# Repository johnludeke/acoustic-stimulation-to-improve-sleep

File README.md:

# Acoustic Stimulation to Improve Sleep

This repo will contain all code and notebooks related to our senior design project.

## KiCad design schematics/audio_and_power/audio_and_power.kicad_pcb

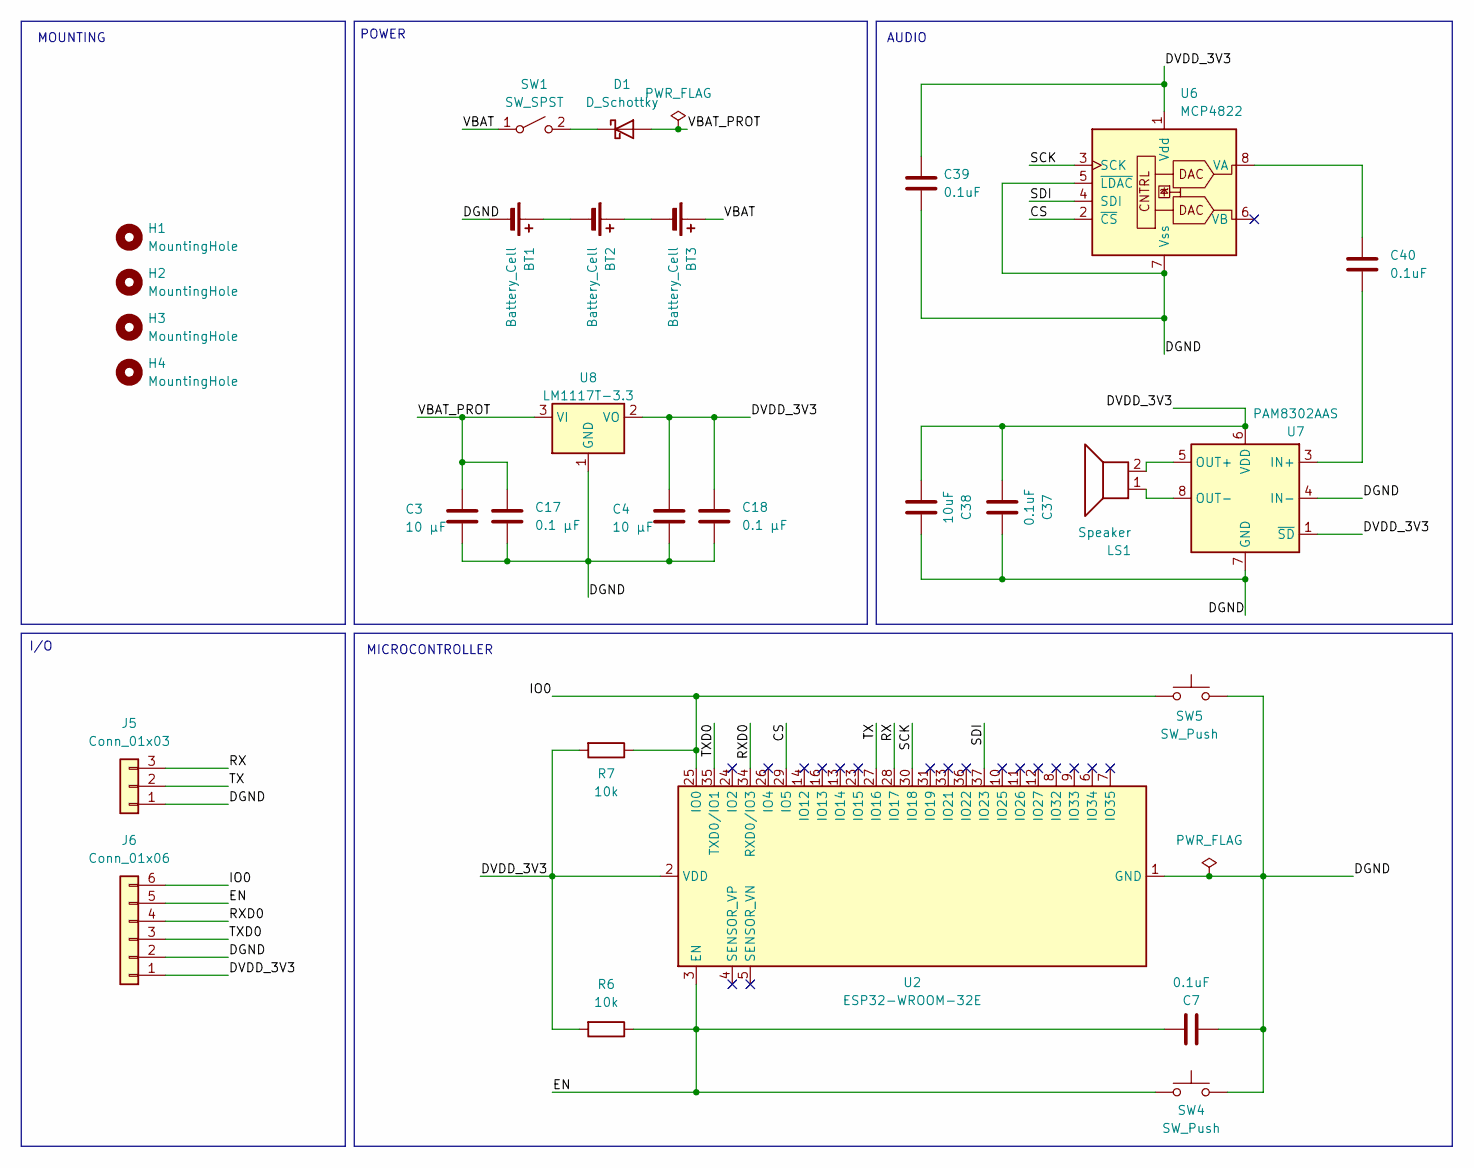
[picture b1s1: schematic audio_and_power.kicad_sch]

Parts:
BT1, BT2, BT3: Battery_Cell; PinHeader_1x02_P2.54mm_Vertical
C3, C4: 10 µF; C_0603_1608Metric
C7, C37, C39, C40: 0.1uF; C_0603_1608Metric
C17, C18: 0.1 µF; C_0603_1608Metric
C38: 10uF; C_0805_2012Metric
D1: D_Schottky; D_SOD-123
H1, H2, H3, H4: MountingHole; MountingHole_3.2mm_M3
J5: Conn_01x03; PinHeader_1x03_P2.54mm_Vertical
J6: Conn_01x06; PinHeader_1x06_P2.54mm_Vertical
LS1: Speaker; PinHeader_1x02_P2.54mm_Vertical
R6, R7: 10k; R_0603_1608Metric
SW1: SW_SPST; SW_DIP_SPSTx01_Slide_6.7x4.1mm_W8.61mm_P2.54mm_LowProfile
SW4, SW5: SW_Push; SW_SPST_TL3342
U2: ESP32-WROOM-32E; ESP32-WROOM-32D
U6: MCP4822; MSOP-8_3x3mm_P0.65mm
U7: PAM8302AAS; MSOP-8_3x3mm_P0.65mm
U8: LM1117T-3.3; TO-220-3_Horizontal_TabDown

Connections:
/CS: U2.29 (IO5), U6.2 (~CS)
/DGND: BT1.2 (-), C3.2, C4.2, C7.1, C17.2, C18.2, C37.2, C38.2, C39.2, J5.1, J6.2, SW4.2, SW5.2, U2.1 (GND), U2.15 (GND), U2.38 (GND), U2.39 (GND), U6.5 (~LDAC), U6.7 (Vss), U7.4 (IN-), U7.7 (GND), U8.1 (GND)
/DVDD_3V3: C4.1, C18.1, C37.1, C38.1, C39.1, J6.1, R6.2, R7.2, U2.2 (VDD), U6.1 (Vdd), U7.1 (~SD), U7.6 (VDD), U8.2 (VO)
/EN: C7.2, J6.5, R6.1, SW4.1, U2.3 (EN)
/IO0: J6.6, R7.1, SW5.1, U2.25 (IO0)
/RX: J5.3, U2.28 (IO17)
/RXD0: J6.4, U2.34 (RXD0/IO3)
/SCK: U2.30 (IO18), U6.3 (SCK)
/SDI: U2.37 (IO23), U6.4 (SDI)
/TX: J5.2, U2.27 (IO16)
/TXD0: J6.3, U2.35 (TXD0/IO1)
/VBAT: BT3.1 (+), SW1.1 (A)
/VBAT_PROT: C3.1, C17.1, D1.2 (A), U8.3 (VI)
unnamed: BT1.1 (+), BT2.2 (-)
unnamed: BT2.1 (+), BT3.2 (-)
unnamed: D1.1 (K), SW1.2 (B)
unnamed: C40.1, U6.8 (VA)
unnamed: C40.2, U7.3 (IN+)
unnamed: LS1.2, U7.5 (OUT+)
unnamed: LS1.1, U7.8 (OUT-)

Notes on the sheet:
I/O
MOUNTING
AUDIO
MICROCONTROLLER
POWER

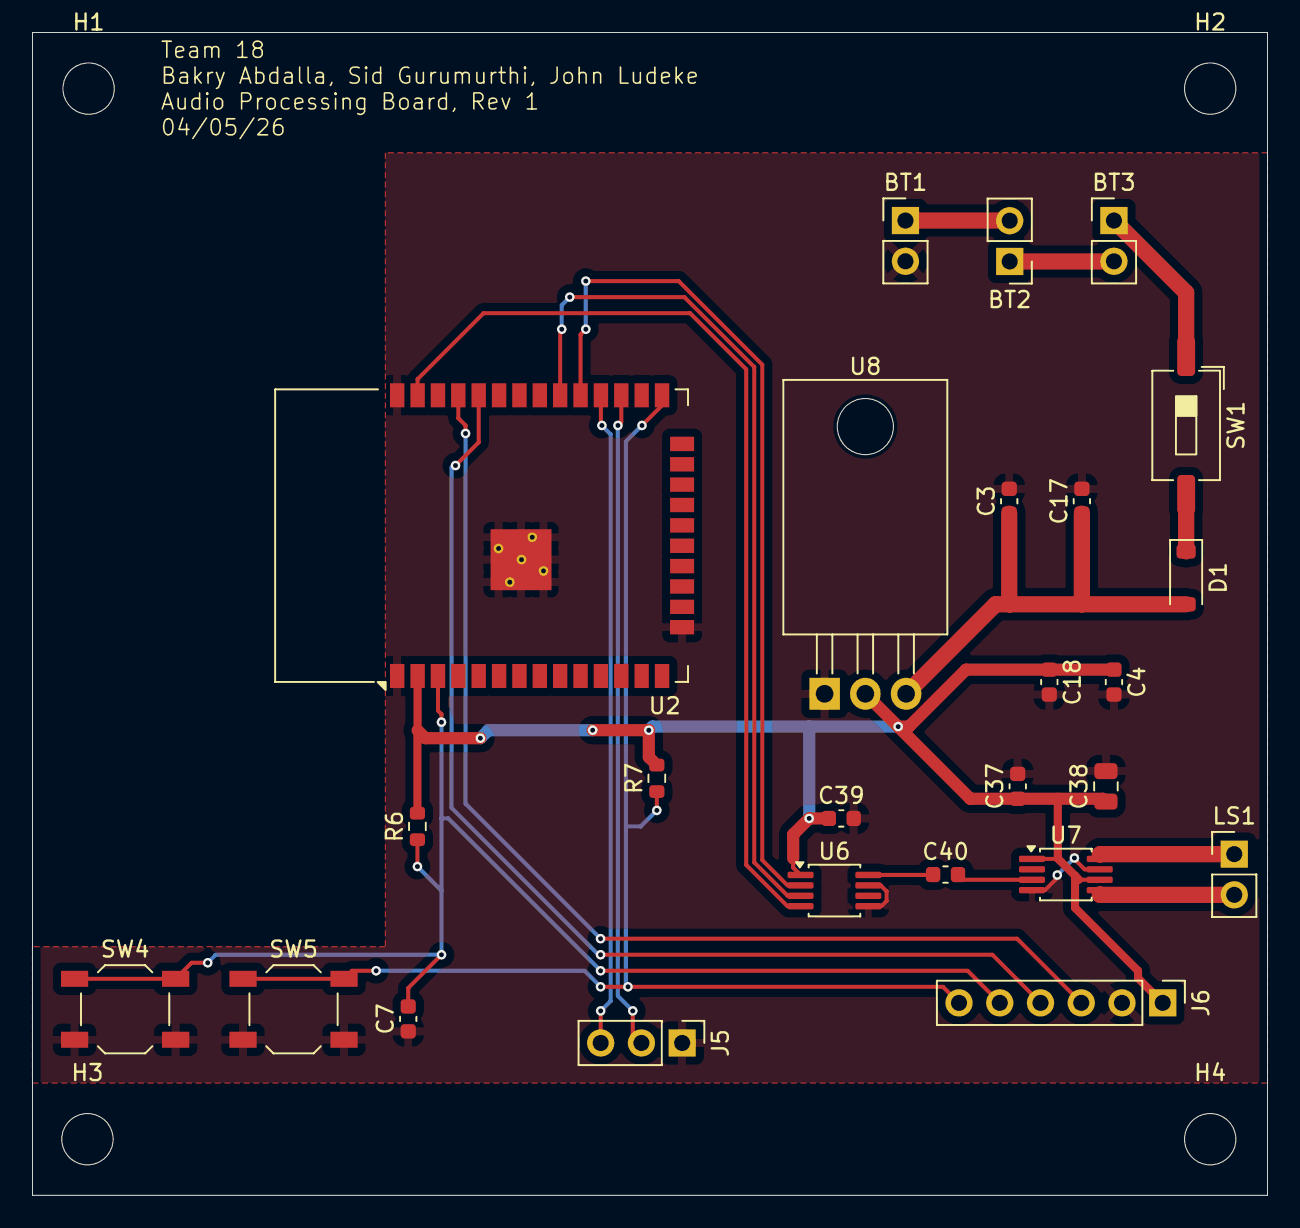
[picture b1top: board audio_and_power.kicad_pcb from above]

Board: 2 copper layers, 77.0 x 72.5 mm, 29 parts (0 on the bottom side), 20 nets.

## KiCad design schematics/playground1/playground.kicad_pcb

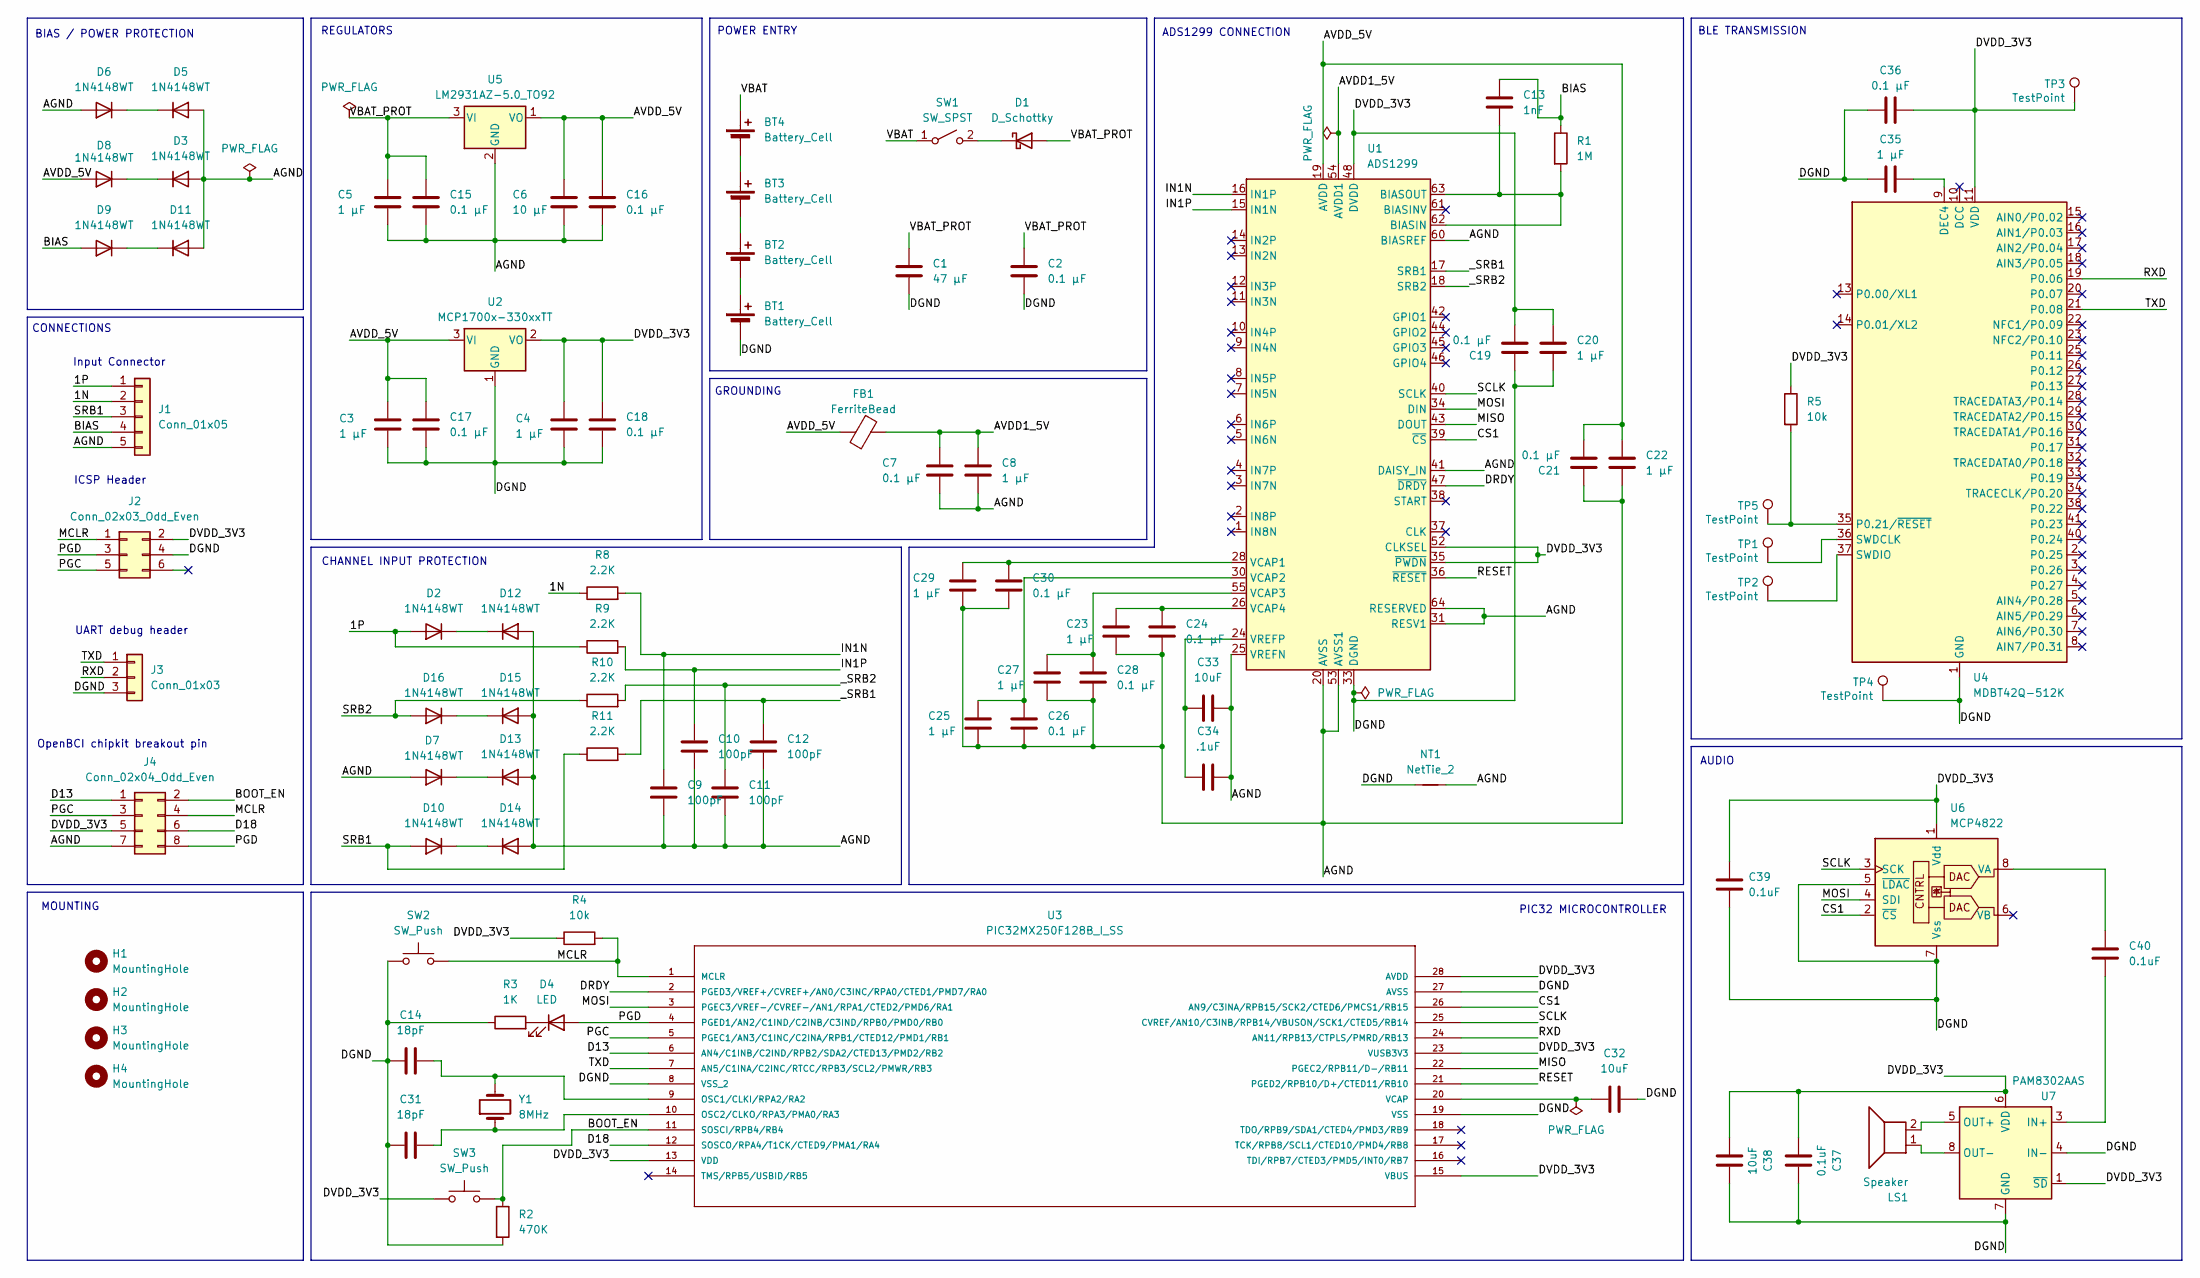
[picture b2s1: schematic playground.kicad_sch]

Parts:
BT1, BT2, BT3, BT4: Battery_Cell; PinHeader_1x02_P2.54mm_Vertical
C1: 47 µF; CP_Radial_D6.3mm_P2.50mm
C2, C7, C15, C16, C17, C18, C19, C21, C24, C26, C28, C30, C36: 0.1 µF; C_0603_1608Metric
C3, C4, C5, C8, C20, C22, C23, C25, C27, C29, C35: 1 µF; C_0603_1608Metric
C6: 10 µF; C_0805_2012Metric
C9, C10, C11, C12: 100pF; C_0603_1608Metric
C13: 1nF; C_0603_1608Metric
C14, C31: 18pF; C_0603_1608Metric
C32, C33, C38: 10uF; C_0805_2012Metric
C34: .1uF; C_0603_1608Metric
C37, C39, C40: 0.1uF; C_0603_1608Metric
D1: D_Schottky; D_SOD-123
D2, D3, D5, D6, D7, D8, D9, D10, D11, D12, D13, D14, D15, D16: 1N4148WT; D_SOD-523
D4: LED; LED_0603_1608Metric_Pad1.05x0.95mm_HandSolder
FB1: FerriteBead; L_0603_1608Metric
H1, H2, H3, H4: MountingHole; MountingHole_3.2mm_M3
J1: Conn_01x05; PinHeader_1x05_P2.54mm_Vertical
J2: Conn_02x03_Odd_Even; PinHeader_2x03_P2.54mm_Vertical
J3: Conn_01x03; PinHeader_1x03_P2.54mm_Vertical
J4: Conn_02x04_Odd_Even; PinHeader_2x04_P2.54mm_Vertical
LS1: Speaker; PinHeader_1x02_P2.54mm_Vertical
NT1: NetTie_2; NetTie-2_SMD_Pad0.5mm
R1: 1M; R_0603_1608Metric
R2: 470K; R_0603_1608Metric
R3: 1K; R_0603_1608Metric
R4, R5: 10k; R_0603_1608Metric
R8, R9, R10, R11: 2.2K; R_0603_1608Metric
SW1: SW_SPST; SW_DIP_SPSTx01_Slide_6.7x4.1mm_W8.61mm_P2.54mm_LowProfile
SW2, SW3: SW_Push; SW_SPST_EVQP0
TP1, TP2, TP3, TP4, TP5: TestPoint; TestPoint_Pad_D1.0mm
U1: ADS1299; TQFP-64_10x10mm_P0.5mm
U2: MCP1700x-330xxTT; SOT-23
U3: PIC32MX250F128B_I_SS; SSOP-28_5.3x10.2mm_P0.65mm
U4: MDBT42Q-512K; Raytac_MDBT42Q
U5: LM2931AZ-5.0_TO92; TO-92_Inline
U6: MCP4822; MSOP-8_3x3mm_P0.65mm
U7: PAM8302AAS; MSOP-8_3x3mm_P0.65mm
Y1: 8MHz; Crystal_SMD_3225-4Pin_3.2x2.5mm

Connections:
/1N: J1.2, R8.1
/1P: D2.2 (A), J1.1, R9.1
/AGND: C5.2, C6.1, C7.2, C8.2, C9.2, C10.2, C11.2, C12.2, C15.2, C16.2, C21.1, C22.2, C23.2, C24.2, C25.2, C26.2, C27.2, C28.2, C29.2, C30.2, C33.2, C34.1, D3.2 (A), D5.2 (A), D6.2 (A), D7.2 (A), D11.2 (A), D12.2 (A), D13.2 (A), D14.2 (A), D15.2 (A), J1.5, J4.7, NT1.2, U1.20 (AVSS), U1.23 (AVSS), U1.25 (VREFN), U1.31 (RESV1), U1.32 (AVSS), U1.41 (DAISY_IN), U1.53 (AVSS1), U1.57 (AVSS), U1.58 (AVSS), U1.60 (BIASREF), U1.64 (RESERVED), U5.2 (GND)
/AVDD1_5V: C7.1, C8.1, FB1.1, U1.54 (AVDD1)
/AVDD_5V: C3.1, C6.2, C16.1, C17.1, C21.2, C22.1, D8.2 (A), FB1.2, U1.19 (AVDD), U1.21 (AVDD), U1.22 (AVDD), U1.56 (AVDD), U1.59 (AVDD), U2.3 (VI), U5.1 (VO)
/BIAS: C13.1, D9.2 (A), J1.4, R1.1
/BOOT_EN: J4.2, R2.1, SW3.2, U3.11 (SOSCI/RPB4/RB4)
/CS1: U1.39 (~CS), U3.26 (AN9/C3INA/RPB15/SCK2/CTED6/PMCS1/RB15), U6.2 (~CS)
/D13: J4.1, U3.6 (AN4/C1INB/C2IND/RPB2/SDA2/CTED13/PMD2/R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)
/D18: J4.6, U3.12 (SOSCO/RPA4/T1CK/CTED9/PMA1/RA4)
/DGND: BT1.2 (-), C1.2, C2.2, C3.2, C4.2, C14.1, C17.2, C18.2, C19.1, C20.2, C31.2, C32.2, C35.1, C36.1, C37.2, C38.2, C39.2, J2.4, J3.3, NT1.1, R2.2, R3.1, SW2.1, TP4.1, U1.33 (DGND), U1.49 (DGND), U1.51 (DGND), U2.1 (GND), U3.8 (VSS_2), U3.19 (VSS), U3.27 (AVSS), U4.1 (GND), U4.12 (GND), U4.24 (GND), U4.39 (GND), U6.5 (~LDAC), U6.7 (Vss), U7.4 (IN-), U7.7 (GND)
/DRDY: U1.47 (~DRDY), U3.2 (PGED3/VREF+/CVREF+/AN0/C3INC/RPA0/CTED1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)
/DVDD_3V3: C4.1, C18.1, C19.2, C20.1, C36.2, C37.1, C38.1, C39.1, J2.2, J4.5, R4.1, R5.1, SW3.1, TP3.1, U1.35 (~PWDN), U1.48 (DVDD), U1.50 (DVDD), U1.52 (CLKSEL), U2.2 (VO), U3.13 (VDD), U3.15 (VBUS), U3.23 (VUSB3V3), U3.28 (AVDD), U4.11 (VDD), U6.1 (Vdd), U7.1 (~SD), U7.6 (VDD)
/IN1N: C9.1, R8.2, U1.16 (IN1P)
/IN1P: C10.1, R9.2, U1.15 (IN1N)
/MCLR: J2.1, J4.4, R4.2, SW2.2, U3.1 (MCLR)
/MISO: U1.43 (DOUT), U3.22 (PGEC2/RPB11/D-/RB11)
/MOSI: U1.34 (DIN), U3.3 (PGEC3/VREF-/CVREF-/AN1/RPA1/CTED2/PMD6/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), U6.4 (SDI)
/PGC: J2.5, J4.3, U3.5 (PGEC1/AN3/C1INC/C2INA/RPB1/CTED12/PMD1/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)
/PGD: D4.2 (A), J2.3, J4.8, U3.4 (PGED1/AN2/C1IND/C2INB/C3IND/RPB0/PMD0/R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)
/RESET: U1.36 (~RESET), U3.21 (PGED2/RPB10/D+/CTED11/RB10)
/RXD: J3.2, U3.24 (AN11/RPB13/CTPLS/PMRD/RB13), U4.19 (P0.06)
/SCLK: U1.40 (SCLK), U3.25 (CVREF/AN10/C3INB/RPB14/VBUSON/SCK1/CTED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), U6.3 (SCK)
/SRB1: D10.2 (A), J1.3, R11.1
/SRB2: D16.2 (A), R10.1
/TXD: J3.1, U3.7 (AN5/C1INA/C2INC/RTCC/RPB3/SCL2/PMWR/RB3), U4.21 (P0.08)
/VBAT: BT4.1 (+), SW1.1 (A)
/VBAT_PROT: C1.1, C2.1, C5.1, C15.1, D1.2 (A), U5.3 (VI)
/_SRB1: C12.1, R11.2, U1.17 (SRB1)
/_SRB2: C11.1, R10.2, U1.18 (SRB2)
unnamed: BT1.1 (+), BT2.2 (-)
unnamed: BT2.1 (+), BT3.2 (-)
unnamed: BT3.1 (+), BT4.2 (-)
unnamed: D1.1 (K), SW1.2 (B)
unnamed: D3.1 (K), D8.1 (K)
unnamed: D4.1 (K), R3.2
unnamed: D5.1 (K), D6.1 (K)
unnamed: D10.1 (K), D14.1 (K)
unnamed: D9.1 (K), D11.1 (K)
unnamed: D2.1 (K), D12.1 (K)
unnamed: D7.1 (K), D13.1 (K)
unnamed: D15.1 (K), D16.1 (K)
unnamed: C13.2, R1.2, U1.62 (BIASIN), U1.63 (BIASOUT)
unnamed: C29.1, C30.1, U1.28 (VCAP1)
unnamed: C25.1, C26.1, U1.30 (VCAP2)
unnamed: C27.1, C28.1, U1.55 (VCAP3)
unnamed: C23.1, C24.1, U1.26 (VCAP4)
unnamed: C33.1, C34.2, U1.24 (VREFP)
unnamed: C14.2, U3.9 (OSC1/CLKI/RPA2/RA2), Y1.2
unnamed: C31.1, U3.10 (OSC2/CLKO/RPA3/PMA0/RA3), Y1.1
unnamed: C32.1, U3.20 (VCAP)
unnamed: C35.2, U4.9 (DEC4)
unnamed: R5.2, TP5.1, U4.35 (P0.21/~RESET)
unnamed: TP1.1, U4.36 (SWDCLK)
unnamed: TP2.1, U4.37 (SWDIO)
unnamed: C40.1, U6.8 (VA)
unnamed: C40.2, U7.3 (IN+)
unnamed: LS1.2, U7.5 (OUT+)
unnamed: LS1.1, U7.8 (OUT-)

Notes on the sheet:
CHANNEL INPUT PROTECTION
MOUNTING
UART debug header
POWER ENTRY
CONNECTIONS
Input Connector
AUDIO
BIAS / POWER PROTECTION
GROUNDING
ICSP Header
REGULATORS
OpenBCI chipkit breakout pin
PIC32 MICROCONTROLLER
ADS1299 CONNECTION
BLE TRANSMISSION

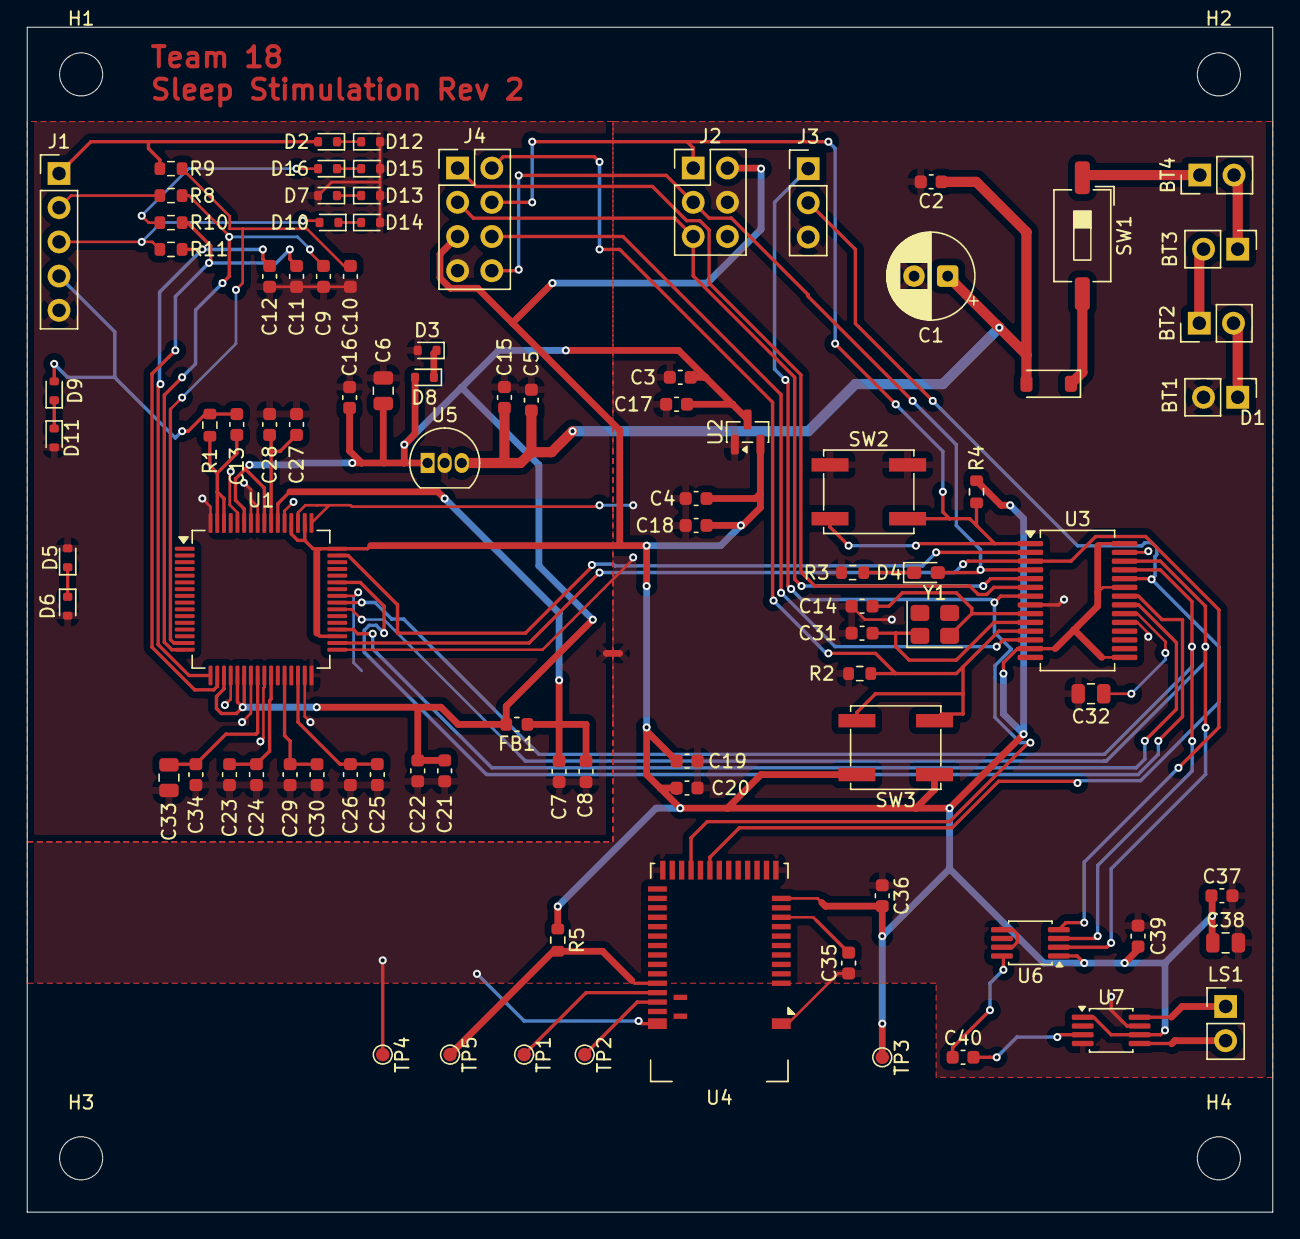
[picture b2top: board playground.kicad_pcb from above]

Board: 2 copper layers, 92.5 x 88.0 mm, 96 parts (0 on the bottom side), 59 nets.

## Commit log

2026-02-17 added empty notebooks for each team member
2026-02-27 Update notebook for bakryha2
2026-02-27 Create README.md for project documentation
    Added a README.md file documenting the progress and updates on the design document and subsystem development for the project.
2026-03-02 IP - work on integrating pic32
2026-03-05 first draft of pic32 schematic complete
2026-03-05 channel input protection
2026-03-05 channel input protection + bias/power protection
2026-03-05 update voltage regulators to ones we can buy
2026-03-05 consolidate schematics into one file
2026-03-05 fix some errors
2026-03-06 fixed label not connected ERC errors
2026-03-06 fixed remaining pin/power errors
2026-03-10 update w/ footprints
2026-03-11 organize PCB, add AGND and DGND nets, but no wiring
2026-03-12 wiring and generating gerber files
2026-03-12 alternate pcb layout
2026-03-12 wiring alternate layout, agnd side
2026-03-12 schematic edits
2026-03-12 change power subsystem to be dgnd, generate gerbers
2026-03-12 pcb sent
2026-03-23 added audio arduino code from breadboard demo
2026-03-23 Update README with recent project developments
    Expanded the README to include recent updates and notes on the design document, signal processing subsystem, and PCB development.
2026-03-23 Revise README with latest project updates
    Updated the README with recent development notes and design decisions regarding the PCB and signal processing subsystem.
2026-03-23 Revise README with PCB routing and design updates
    Updated README with recent PCB development notes and design decisions.
2026-03-23 fixing unconnected items drc errors
2026-03-24 AGND connection issues fixed
2026-03-25 dgnd connection errors, some fixed
2026-03-25 Update README with recent PCB and design notes
    Added recent updates and fixes for dgnd and agnd pin connections. Included detailed notes on PCB design, component selection, and signal processing subsystem development.
2026-03-25 avdd fixes
2026-03-26 fixed all errors for pcb with no audio or ble
2026-03-26 add bluetooth chip to schematic and pcb
2026-03-26 updated revision number for pcb
2026-03-26 audio subsystem added in schematic + footprints
2026-03-26 clean up audio schematic, wire audio in and move ble
2026-03-26 updated pink nonise code to take into account dac
2026-03-26 changed resistor and capacitor combination component to individual capacitors and resistors
2026-03-26 add tracing for new resistor / diode arrays
2026-03-26 traced pcb audio subsys edits
2026-03-26 ensuring schematic pushed
2026-03-31 resolve changes
2026-04-04 added ardino code to listen to eeg data from the cytonboard/eeg headset combo
2026-04-06 create new audio processor schematic + pcb + gerbers
2026-04-06 change hole sizes for pcb ordering
2026-04-06 arduino code to plot eeg channels
2026-04-06 change hole size on esp32
2026-04-06 reformat files. create pink noise generator based off waves
2026-04-07 few updates to random things
2026-04-08 Revise README with project updates and insights
    Updated README with detailed project notes and progress on EEG signal processing and hardware integration.
2026-04-08 Revise README for project updates and design changes
    Updated README with detailed progress on packet parsing, signal validation, and design direction pivot for EEG data processing. Included insights on hardware integration and SWS detection algorithm i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
2026-04-09 drill files
2026-04-14 python prototype for feature extraction
2026-04-19 python prototype of linear regression, MLP models for SWS prediction, expanding on feature extraction script
2026-04-24 new code for custom pcb
2026-04-24 updated python script with visuals for: fft of sws epoch, bandpass filtering in time domain to find dominant sws oscillation frequency, using that + trough detection to estimate peaks, peaks are wher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
2026-04-26 code for just playing flat noise
2026-04-26 delivering and plotting phase-aligned audio stim (works with breadboard)
2026-04-27 cleanup some files
2026-04-27 add webapp code and update arduino code to send to webapp instead of python
2026-04-27 change sids code to work with pcb
2026-04-27 extended plot_eeg_channels to do zcp feature vector and sws prediction with non zero probability
2026-04-27 add upload of recording to web app
2026-05-04 updating this notebook with entries (i use my notes app)
2026-05-05 update notebook
    update notebook
2026-05-05 update notebook
2026-05-05 Update output message from 'Hello World' to 'Goodbye World'
2026-05-05 Update fmt.Println message from 'Hello' to 'Goodbye'
2026-05-05 Update greeting from 'Hello World' to 'Goodbye World'
2026-05-05 references
2026-05-05 code snippet formatting
2026-05-05 Update references
2026-05-05 Update print statement from 'Hello' to 'Goodbye'
2026-05-07 Update bakry's notebook
2026-05-08 header size
2026-05-08 finalize notebook
